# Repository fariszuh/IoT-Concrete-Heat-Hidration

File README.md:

# Heat Hydration

## Latar Belakang

Perilaku struktur beton pada gedung sangat dipengaruhi oleh mutunya. Salah satu faktor internal beton yang dapat menurunkan kualitas mutu beton adalah panas hidrasi (Lu et al., 2020). Panas akibat proses hidrasi sulit dilepaskan oleh
beton karena sifat konduktivitas beton yang rendah sehingga terjadi perbedaan suhu antara beton dan lingkungan yang besar seiring peningkatan suhu hidrasi
(Gowripalan, 2020). Perbedaan suhu ini mengakibatkan peristiwa konveksi yang menimbulkan tegangan tarik pada sisi luar dan tegangan tekan di bagian tengah  beton. Tegangan ini disebut dengan tegangan thermal. Tegangan thermal yang tidak mampu diterima pada umur awal beton menyebabkan retak yang terjadi bersamaan dengan susut. Retakan dan susut mengubah sifat mekanik beton sehingga terjadi penurunan mutu beton (Gowripalan, 2020).
Mutu beton yang berubah penting untuk diketahui dengan cara evaluasi yang ditinjau dengan Indeks kematangan beton. Evaluasi ini didasari oleh hasil monitoring kenaikan suhu dan perubahan susut beton sebagai efek dari panas hidrasi sejak umur awal.
Monitoring kenaikan suhu dan perubahan susut merupakan hal yang penting diperhatikan dalam mengevaluasi mutu beton. Namun, sistem akuisisi yang digunakan untuk monitoring masih menggunakan transfer data dari data logger menuju komputer atau bahkan dicatat secara manual. Akuisisi data dengan sistem ini berisiko mudah mengalami kehilangan data record karena pada kondisi monitoring realtime terdapat banyak gangguan dan kurang praktis karena data tidak dapat dipantau secara jarak jauh serta memerlukan komputer yang harus menyala ketika monitoring, yang mana monitoring dilakukan selama 24 jam.
Inovasi yang diberikan untuk permasalahan tersebut adalah perancangan sistem monitoring dengan automasi transfer data ke cloud database sebagai wadah penyimpanan dan pengolahan data. Transfer data dari penyimpanan internal dapat dilakukan secara otomatis atau dikendalikan oleh pengguna saat terdapat jaringan internet. Data input yang telah ditransfer, diolah dalam pemrograman untuk mendapatkan maturity index berupa grafik yang akan dibandingkan antara data lab dan lapangan sebagai tinjauan evaluasi kematangan beton akibat efek panas hidrasi. Selain itu, perubahan susut dapat diklasifikasikan berdasarkan waktu yang berjalan dan kondisi kenaikan suhu. Adapun, Modifikasi pada instrumen susut yang menggunakan prinsip sinyal impuls pada kaliper digital yang bekerja bersamaan dengan pengukuran suhu oleh sensor thermocouple. Implementasi ide ini diharapkan dapat menjawab masalah tersebut  yang mana proses perwujudan ide akan dijelaskan dalam laporan ini.

## Rumusan Masalah

Masalah yang dapat dirumuskan dari latar belakang di atas adalah sebagai
berikut.

1. Merancang purwarupa dan algoritma sistem untuk mengukur parameter evaluasi mutu beton (suhu dan susut) pada umur awal akibat efek panas
hidrasi berbasis wireless?
2. Bagaimana cara kerja sistem akuisisi data sehingga dapat menjadi indikator evaluasi mutu beton pada umur awal akibat efek panas hidrasi?
3. Bagaimana menciptakan visualisasi dari sistem akuisisi data parameter evaluasi mutu beton pada umur awal akibat efek panas hidrasi berbasis wireless?

## Tujuan

Tujuan yang akan dicapai dari Program Kreativitas Mahasiswa ini adalah
sebagai berikut.
1. Merancang purwarupa dan algoritma sistem untuk mengukur parameter
evaluasi mutu beton (suhu dan susut) pada umur awal akibat efek panas
hidrasi berbasis wireless.
2. Mengetahui cara kerja sistem akuisisi data sehingga dapat menjadi
indikator evaluasi mutu beton pada umut awal akibat efek panas hidrasi.
3. Menciptakan visualisasi sistem akuisisi data parameter evaluasi mutu
beton pada umur awal akibat panas hidrasi berbasis wireless.

## Manfaat Program
Manfaat dari program Kreativitas Mahasiswa ini adalah sebagai berikut.

1. Bagi Pelaksana
Tercapainya peran dan fungsi mahasiswa untuk be eran pada masyarakat  dan bidang keilmuannya.

2. Bagi Akademisi
Menunjang riset terkait inovasi beton yang mengkaji panas hidrasi sebagai properties beton.

3. Bagi Industri Konstruksi
a. Mempermudah monitoring dan evaluasi mutu beton dengan sistem yang lebih akurat dan praktis.
b. Adanya riwayat pengujian pada penyimpanan awan akan membantu dalam pencarian problem pada sistem struktural pekerjaan konstruksi.

## Hasil pengujian dan evaluasi
Hasil dan evaluasi yang diperoleh dari pengujian alat meliputi: 

### Hasil pengambilan data thermocouple tipe K tersaji dalam grafik berikut

Gambar 4. 6 Kalibrasi Pengukuran Suhu

Error thermocouple terukur rata-rata sebesar 0.8025°C (absolute). Hal ini menandakan bahwa standar pengukuran <5% dari range 60°C sudah te enuhi atau bernilai < 3°C. 

### Hasil pengujian Panjang susut tersaji pada grafik berikut. 

Gambar 4. 7 Kalibrasi Pengukuran Susut

Error pengukuran digital caliper diperoleh sebesar 252.142857 µm. Nilai error ini masih jauh dari harapan, yakni sesuai standar 10 µm. ketidaksesuaian ini dimungkinkan terjadi karena kontak multiple elektrode stator (tembaga) dengan jalur slider (sin-cos plate) pada PCB terkadang bergeser vertical (normalnya hanya bergeser horizontal sepanjang tuas caliper) sehingga menyebabkan adanya gap antar plate dan timbul noise capacitance. Gap ini dimungkinkan terjadi karena pemasangan caliper dan kabel extender ke modul memakan jalur gerak tuas caliper sehingga jika dilihat dari sisi mekanikal akan sedikit menganga.

### Hasil percobaan monitoring dari sampel beton mutu 25 MPa yang dibuat memperoleh hasil sebagai berikut. 

Data hasil pengukuran suhu oleh termokopel disajikan pada gambar 4.8 dan data pengukuran susut oleh digital caliper disajikan oleh gambar 4.10. Untuk memperoleh prediksi kuat tekan beton digunakan nilai suhu yang dimasukkan kedalam persamaan Nurse-Saul dan diperoleh plot grafik perbandingan kuat tekan terhadap umur beton.

Gambar 4. 8 Hasil Monitoring Suhu Beton

Gambar 4. 9 Hasil Ploting Grafik Indeks Kematangan Beton

Gambar 4. 10 Hasil Monitoring Susut Beton

## Kesimpulan
Sistem yang kami buat merupakan sistem akuisisi data berbasis wireless untuk evaluasi efek panas hidrasi beton pada umur awal. Data hasil pengukuran dan monitoring parameter panas hidrasi akan dikirim pada penyimpanan cloud. Sehingga dapat diakses secara realtime melalui website. Adapun alat yang kami buat berhasil diimplementasikan pada sampel beton mutu 25 MPa. Akan tetapi, dari hasil evaluasi diperoleh nilai eror rata-rata pembacaan suhu sebesar 0.8025˚C dan eror pembacaan susut sebesar 0,25mm dibandingkan dengan alat yang terkalibrasi.

## Saran
Saran kami dalam mewujudkan pengembangan alat ini menuju arah yang lebih baik adalah mempertimbangkan sensor dengan ketelitian yang lebih baik atau lebih mendalami cara meningkatkan kualitas pengukuran. Selain itu, perlu adanya kerja sama dengan pihak lain agar pengembangkan alat mampu diimplementasikan di lapangan dan potensi khusus dapat tercapai.

## Dokumentasi PKM (Youtube Ditmawa ITS 2022)
Dokumentasi ada pada direktori Luaran PKM (Video dan Audio). 

Link youtube:
https://www.youtube.com/watch?v=sR6Rn05YM_g&ab_channel=DirektoratKemahasiswaanITS

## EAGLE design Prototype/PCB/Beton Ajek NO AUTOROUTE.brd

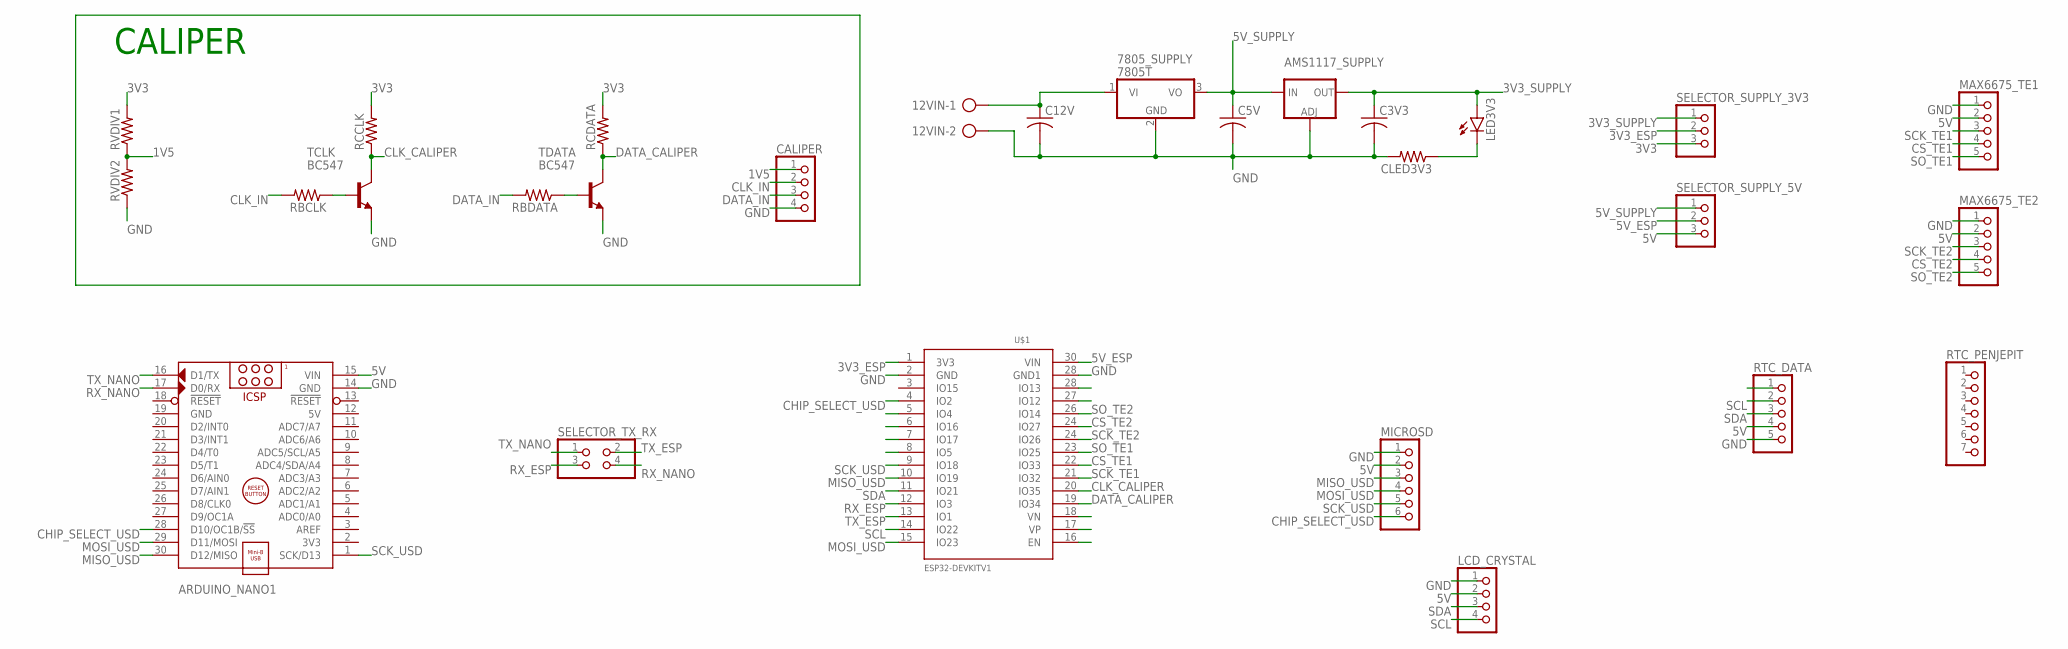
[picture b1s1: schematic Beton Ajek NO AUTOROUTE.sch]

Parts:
12VIN: AK300/2
7805_SUPPLY: 7805T; TO220H
AMS1117_SUPPLY: V_REG_LM1117SOT223; SOT223
ARDUINO_NANO1: ARDUINO_NANO
C3V3, C5V, C12V: C-US075-032X103; C075-032X103
CALIPER: PINHD-1X4; 1X04
CLED3V3: R-US_0207/10; 0207/10
LCD_CRYSTAL: PINHD-1X4; 1X04
LED3V3: LED5MM
MAX6675_TE1, MAX6675_TE2: PINHD-1X5; 1X05
MICROSD: PINHD-1X6; 1X06
RBCLK: R-US_0207/10; 0207/10
RBDATA: R-US_0207/10; 0207/10
RCCLK: R-US_0207/10; 0207/10
RCDATA: R-US_0207/10; 0207/10
RTC_DATA: PINHD-1X5; 1X05
RTC_PENJEPIT: PINHD-1X7; 1X07
RVDIV1, RVDIV2: R-US_0207/10; 0207/10
SELECTOR_SUPPLY_3V3, SELECTOR_SUPPLY_5V: PINHD-1X3; 1X03
SELECTOR_TX_RX: PINHD-2X2; 2X02
TCLK: BC547; TO92
TDATA: BC547; TO92
U$1: ESP32DEVKITV1; ESP32-DEVKITV1

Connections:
1V5: CALIPER.1, RVDIV1.1, RVDIV2.2
3V3: RCCLK.2, RCDATA.2, RVDIV1.2, SELECTOR_SUPPLY_3V3.3
3V3_ESP: SELECTOR_SUPPLY_3V3.2, U$1.1 (3V3)
3V3_SUPPLY: AMS1117_SUPPLY.2 (OUT), AMS1117_SUPPLY.4 (OUT), C3V3.1, LED3V3.A, SELECTOR_SUPPLY_3V3.1
5V: ARDUINO_NANO1.12 (5V), ARDUINO_NANO1.15 (VIN), LCD_CRYSTAL.2, MAX6675_TE1.2, MAX6675_TE2.2, MICROSD.2, RTC_DATA.4, SELECTOR_SUPPLY_5V.3
5V_ESP: SELECTOR_SUPPLY_5V.2, U$1.30 (VIN)
5V_SUPPLY: 7805_SUPPLY.3 (VO), AMS1117_SUPPLY.3 (IN), C5V.1, SELECTOR_SUPPLY_5V.1
CHIP_SELECT_USD: ARDUINO_NANO1.28 (D10/OC1B/!SS), MICROSD.6, U$1.4 (IO2)
CLK_CALIPER: RCCLK.1, TCLK.3 (C), U$1.20 (IO35)
CLK_IN: CALIPER.2, RBCLK.2
CS_TE1: MAX6675_TE1.4, U$1.22 (IO33)
DATA_CALIPER: RCDATA.1, TDATA.3 (C), U$1.19 (IO34)
DATA_IN: CALIPER.3, RBDATA.2
MISO_USD: ARDUINO_NANO1.30 (D12/MISO), MICROSD.3, U$1.10 (IO19)
MOSI_USD: ARDUINO_NANO1.29 (D11/MOSI), MICROSD.4, U$1.15 (IO23)
unnamed: 12VIN.1, 7805_SUPPLY.1 (VI), C12V.1
unnamed: RBCLK.1, TCLK.2 (B)
unnamed: CLED3V3.1, LED3V3.K (C)
unnamed: RBDATA.1, TDATA.2 (B)
RX_ESP: SELECTOR_TX_RX.3, U$1.12 (IO3)
RX_NANO: ARDUINO_NANO1.17 (D0/RX), SELECTOR_TX_RX.4
SCK_TE1: MAX6675_TE1.3, U$1.21 (IO32)
SCK_USD: ARDUINO_NANO1.1 (SCK/D13), MICROSD.5, U$1.9 (IO18)
SCL: LCD_CRYSTAL.4, RTC_DATA.2, U$1.14 (IO22)
SDA: LCD_CRYSTAL.3, RTC_DATA.3, U$1.11 (IO21)
SO_TE1: MAX6675_TE1.5, U$1.23 (IO25)
SO_TE2: MAX6675_TE2.5, U$1.26 (IO14)
TX_ESP: SELECTOR_TX_RX.2, U$1.13 (IO1)
TX_NANO: ARDUINO_NANO1.16 (D1/TX), SELECTOR_TX_RX.1

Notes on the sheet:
CALIPER

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
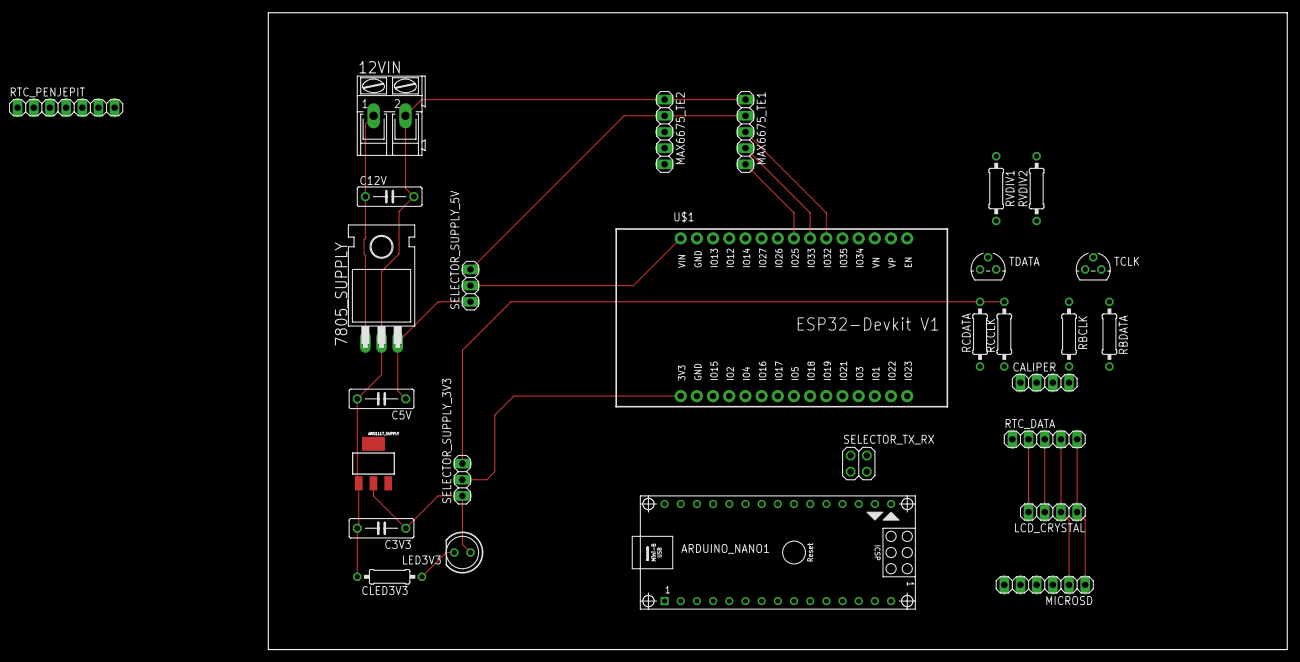
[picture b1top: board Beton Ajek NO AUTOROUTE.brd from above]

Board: 2 copper layers, 160.0 x 100.0 mm, 28 parts (0 on the bottom side), 32 nets.

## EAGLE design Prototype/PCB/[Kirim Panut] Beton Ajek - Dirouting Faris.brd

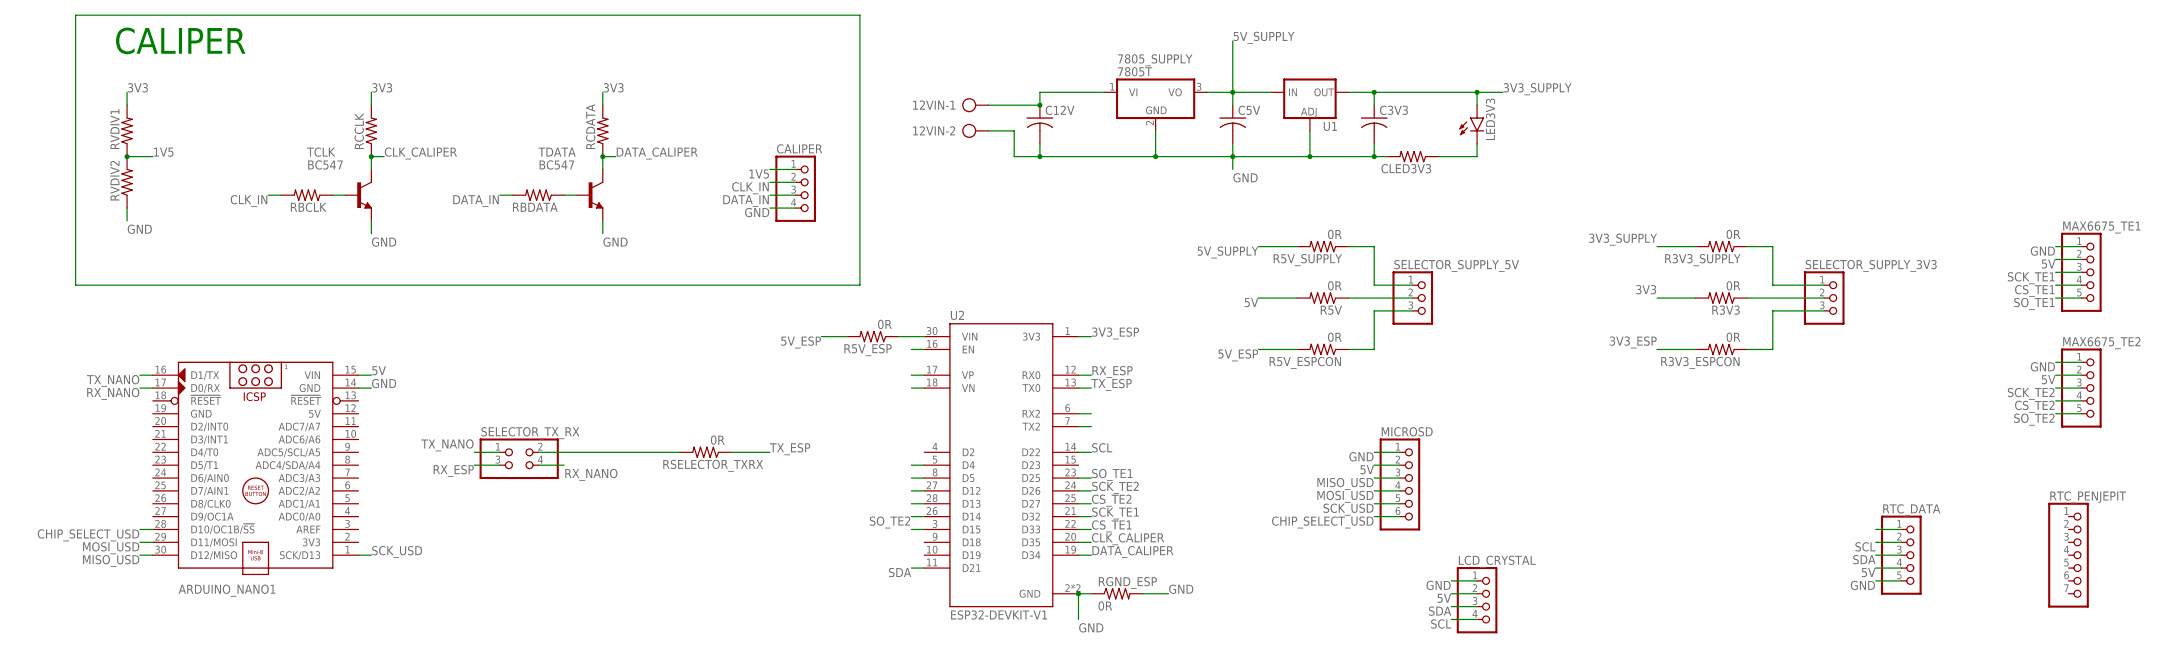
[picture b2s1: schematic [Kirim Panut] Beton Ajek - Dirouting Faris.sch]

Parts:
12VIN: AK300/2
7805_SUPPLY: 7805T; TO220H
ARDUINO_NANO1: ARDUINO_NANO
C3V3, C5V, C12V: C-US075-032X103; C075-032X103
CALIPER: PINHD-1X4; 1X04
CLED3V3: R-US_0207/10; 0207/10
LCD_CRYSTAL: PINHD-1X4; 1X04
LED3V3: LED5MM
MAX6675_TE1, MAX6675_TE2: PINHD-1X5; 1X05
MICROSD: PINHD-1X6; 1X06
R3V3, R3V3_ESPCON, R3V3_SUPPLY, R5V, R5V_ESP, R5V_ESPCON, R5V_SUPPLY: 0R; 0207/10
RBCLK: R-US_0207/10; 0207/10
RBDATA: R-US_0207/10; 0207/10
RCCLK: R-US_0207/10; 0207/10
RCDATA: R-US_0207/10; 0207/10
RGND_ESP: 0R; 0207/15
RSELECTOR_TXRX: 0R; 0207/10
RTC_DATA: PINHD-1X5; 1X05
RTC_PENJEPIT: PINHD-1X7; 1X07
RVDIV1, RVDIV2: R-US_0207/10; 0207/10
SELECTOR_SUPPLY_3V3, SELECTOR_SUPPLY_5V: PINHD-1X3; 1X03
SELECTOR_TX_RX: PINHD-2X2; 2X02
TCLK: BC547; TO92
TDATA: BC547; TO92
U1: V_REG_LM1117SOT223; SOT223
U2: ESP32-DEVKIT-V1; MODULE_ESP32_DEVKIT_V1

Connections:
1V5: CALIPER.1, RVDIV1.1, RVDIV2.2
3V3: R3V3.2, RCCLK.2, RCDATA.2, RVDIV1.2
3V3_ESP: R3V3_ESPCON.2, U2.1 (3V3)
3V3_SUPPLY: C3V3.1, LED3V3.A, R3V3_SUPPLY.2, U1.2 (OUT), U1.4 (OUT)
5V: ARDUINO_NANO1.12 (5V), ARDUINO_NANO1.15 (VIN), LCD_CRYSTAL.2, MAX6675_TE1.2, MAX6675_TE2.2, MICROSD.2, R5V.2, RTC_DATA.4
5V_ESP: R5V_ESP.2, R5V_ESPCON.2
5V_SUPPLY: 7805_SUPPLY.3 (VO), C5V.1, R5V_SUPPLY.2, U1.3 (IN)
CHIP_SELECT_USD: ARDUINO_NANO1.28 (D10/OC1B/!SS), MICROSD.6
CLK_CALIPER: RCCLK.1, TCLK.3 (C), U2.20 (D35)
CLK_IN: CALIPER.2, RBCLK.2
CS_TE1: MAX6675_TE1.4, U2.22 (D33)
CS_TE2: MAX6675_TE2.4, U2.25 (D27)
DATA_CALIPER: RCDATA.1, TDATA.3 (C), U2.19 (D34)
DATA_IN: CALIPER.3, RBDATA.2
GND: 12VIN.2, 7805_SUPPLY.2 (GND), ARDUINO_NANO1.14 (GND), ARDUINO_NANO1.19 (GND), C3V3.2, C5V.2, C12V.2, CALIPER.4, CLED3V3.2, LCD_CRYSTAL.1, MAX6675_TE1.1, MAX6675_TE2.1, MICROSD.1, RGND_ESP.1, RGND_ESP.2, RTC_DATA.5, RVDIV2.1, TCLK.1 (E), TDATA.1 (E), U1.1 (ADJ), U2.2 (GND), U2.29 (GND)
MISO_USD: ARDUINO_NANO1.30 (D12/MISO), MICROSD.3
MOSI_USD: ARDUINO_NANO1.29 (D11/MOSI), MICROSD.4
unnamed: 12VIN.1, 7805_SUPPLY.1 (VI), C12V.1
unnamed: RBCLK.1, TCLK.2 (B)
unnamed: RSELECTOR_TXRX.2, SELECTOR_TX_RX.2
unnamed: R5V_ESP.1, U2.30 (VIN)
unnamed: R5V.1, SELECTOR_SUPPLY_5V.2
unnamed: R5V_SUPPLY.1, SELECTOR_SUPPLY_5V.1
unnamed: CLED3V3.1, LED3V3.K (C)
unnamed: R5V_ESPCON.1, SELECTOR_SUPPLY_5V.3
unnamed: R3V3.1, SELECTOR_SUPPLY_3V3.2
unnamed: R3V3_SUPPLY.1, SELECTOR_SUPPLY_3V3.1
unnamed: RBDATA.1, TDATA.2 (B)
unnamed: R3V3_ESPCON.1, SELECTOR_SUPPLY_3V3.3
RX_ESP: SELECTOR_TX_RX.3, U2.12 (RX0)
RX_NANO: ARDUINO_NANO1.17 (D0/RX), SELECTOR_TX_RX.4
SCK_TE1: MAX6675_TE1.3, U2.21 (D32)
SCK_TE2: MAX6675_TE2.3, U2.24 (D26)
SCK_USD: ARDUINO_NANO1.1 (SCK/D13), MICROSD.5
SCL: LCD_CRYSTAL.4, RTC_DATA.2, U2.14 (D22)
SDA: LCD_CRYSTAL.3, RTC_DATA.3, U2.11 (D21)
SO_TE1: MAX6675_TE1.5, U2.23 (D25)
SO_TE2: MAX6675_TE2.5, U2.26 (D14)
TX_ESP: RSELECTOR_TXRX.1, U2.13 (TX0)
TX_NANO: ARDUINO_NANO1.16 (D1/TX), SELECTOR_TX_RX.1

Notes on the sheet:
CALIPER

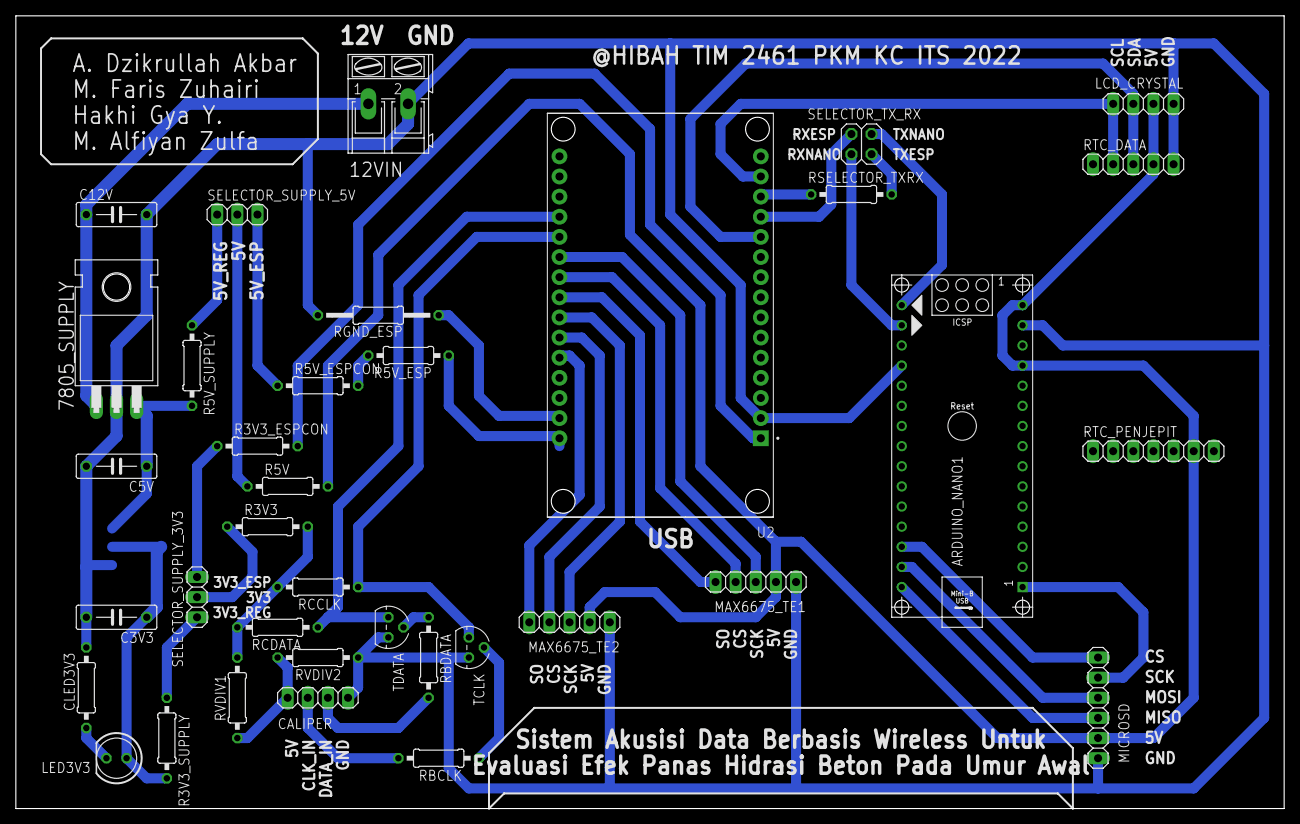
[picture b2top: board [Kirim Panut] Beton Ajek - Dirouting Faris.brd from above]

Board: 2 copper layers, 160.0 x 100.0 mm, 37 parts (1 on the bottom side), 40 nets.

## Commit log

2023-09-28 reformat README.md

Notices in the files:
parts and their libraries:
SparkFun-IC-Power: Licensing: Creative Commons ShareAlike 4.0 International - https://creativecommons.org/licenses/by-sa/4.0
